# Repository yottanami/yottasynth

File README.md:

# Yottasynth: Open Hardware Touchscreen Synth with Persian/Iranian Tunings

Yottasynth is an open hardware touchscreen synth with a compact page-based control surface, five context-sensitive knobs, an arpeggiator, a step sequencer, and support for Persian/Iranian music tunings.

یوتاسینث یک سینت‌سایزر دیجیتال متن‌باز با رابط لمسی، سکوئنسر، آرپژیاتور و پشتیبانی از کوک‌های موسیقی ایرانی است. این ساز امکان انتخاب کوک‌های مرتبط با دستگاه‌ها و آوازهای ایرانی را فراهم می‌کند تا برای اجرا و طراحی صدا در فضای موسیقی ایرانی مناسب‌تر باشد.

## What It Is

The current firmware is a playable mono synth instrument with:

- a touch-first panel UI
- five context-sensitive knobs
- arpeggiator
- 16-step sequencer
- three effect modes: `Echo`, `Reverb`, and `Drive`
- selectable Persian scale tunings

## Current Features

- `PLAY`, `OSC`, `FILT`, `MOD`, `FX`, `ARP`, `SEQ`, and `SET` pages
- mono synth voice with dual oscillators, noise, filter, envelope, glide, and LFO
- page-specific touch actions and knob mappings
- internal BPM transport, or external MIDI clock sync over USB
- arpeggiator with mode, division, gate, octave range, and latch
- 16-step sequencer with step selection, bank switching, swing, and live MIDI record
- effect editing with page-dependent controls
- output volume, tuning, and clock-source (internal / external) selection from the settings page
- Persian scale support through alternate tunings
- touch screen used for navigation and `OK / Confirm` actions

## Persian / Iranian Tunings

The current tuning list includes:

- `Standard` (`استاندارد`)
- `Shur` (`شور`)
- `Abuata` (`ابوعطا`)
- `Dashti` (`دشتی`)
- `Bayat-e Tork` (`بیات ترک`)
- `Afshari` (`افشاری`)
- `Segah` (`سه‌گاه`)
- `Chahargah` (`چهارگاه`)
- `Homayun` (`همایون`)
- `Bayat-e Esfahan` (`بیات اصفهان`)
- `Nava` (`نوا`)
- `Mahur` (`ماهور`)
- `Rast-Panjgah` (`راست‌پنجگاه`)

## How It Works

Yottasynth is organized as one compact panel split into pages. The touch screen is used to switch pages and trigger actions, while the five physical knobs always control the five parameters shown on screen for the current page.

In normal use, a MIDI controller feeds notes into the synth engine through USB host MIDI. You shape the sound on the synth pages, switch to `ARP` for rhythmic note patterns, use `SEQ` for step programming and live record, and adjust global volume or tuning in `SET`. When a destructive action needs confirmation, a second tap on the armed button acts as `OK`.

The transport (sequencer and arpeggiator) normally runs on its own internal BPM. Set `SYNC` to `EXT` on the `SET` page to slave it to an external MIDI clock over USB instead. Two USB paths are supported without any hardware change:

- the **USB host port** (alongside the keyboard, through a USB hub) for standalone gear such as an Ableton Move
- the **native USB port** (the same cable used to upload firmware) for a computer / DAW such as Ableton Live

In external mode the synth follows the host's tempo and its start / stop / continue transport.

## Interface Summary

- top bar: page title plus compact status
- middle panel: parameter cards and touch actions
- bottom bar: eight color-coded tabs

Page layout:

- `PLAY`: quick performance controls
- `OSC`: oscillator mix, noise, octave, detune, and waveform changes
- `FILT`: filter and envelope shaping
- `MOD`: LFO, bend range, and modulation target
- `FX`: echo, reverb, or drive editing
- `ARP`: arpeggiator setup
- `SEQ`: 16-step sequencing
- `SET`: output volume, tuning, clock source (internal / external sync), and input test entry

## User Guide

For a user-perspective walkthrough of the panel, controls, pages, and sequencing flow, see [docs/user-guide.md](docs/user-guide.md).

For developer-facing documentation of the firmware structure and code, see:

- [docs/README.md](docs/README.md)
- [docs/source-reading-guide.md](docs/source-reading-guide.md)
- [docs/codebase-guide.md](docs/codebase-guide.md)

## Screenshots

To export screenshots of the current screen pages without running the device firmware:

```bash
python3 scripts/generate_screenshots.py
```

This writes one SVG per page, a stitched `overview.svg` for the README, and a simple preview index into `docs/screenshots/`.

## Hardware + 3D

- board design files: `etc/board/`
- touch-driven panel firmware: `src/`
- headers and shared definitions: `include/`
- project docs: `docs/`

## Status

This is still an active work-in-progress project, but the firmware already implements the main instrument shell and core performance workflow.

## Contributing

Contributions are welcome. Feel free to open an issue or a PR if you want to help with firmware, hardware, or design.

## Issues

https://github.com/yottanami/yottainst/issues/new

## Contact

https://yottanami.com

## Support

- GitHub Sponsors: https://github.com/sponsors/yottanami
- Ko-fi: https://ko-fi.com/yottanami

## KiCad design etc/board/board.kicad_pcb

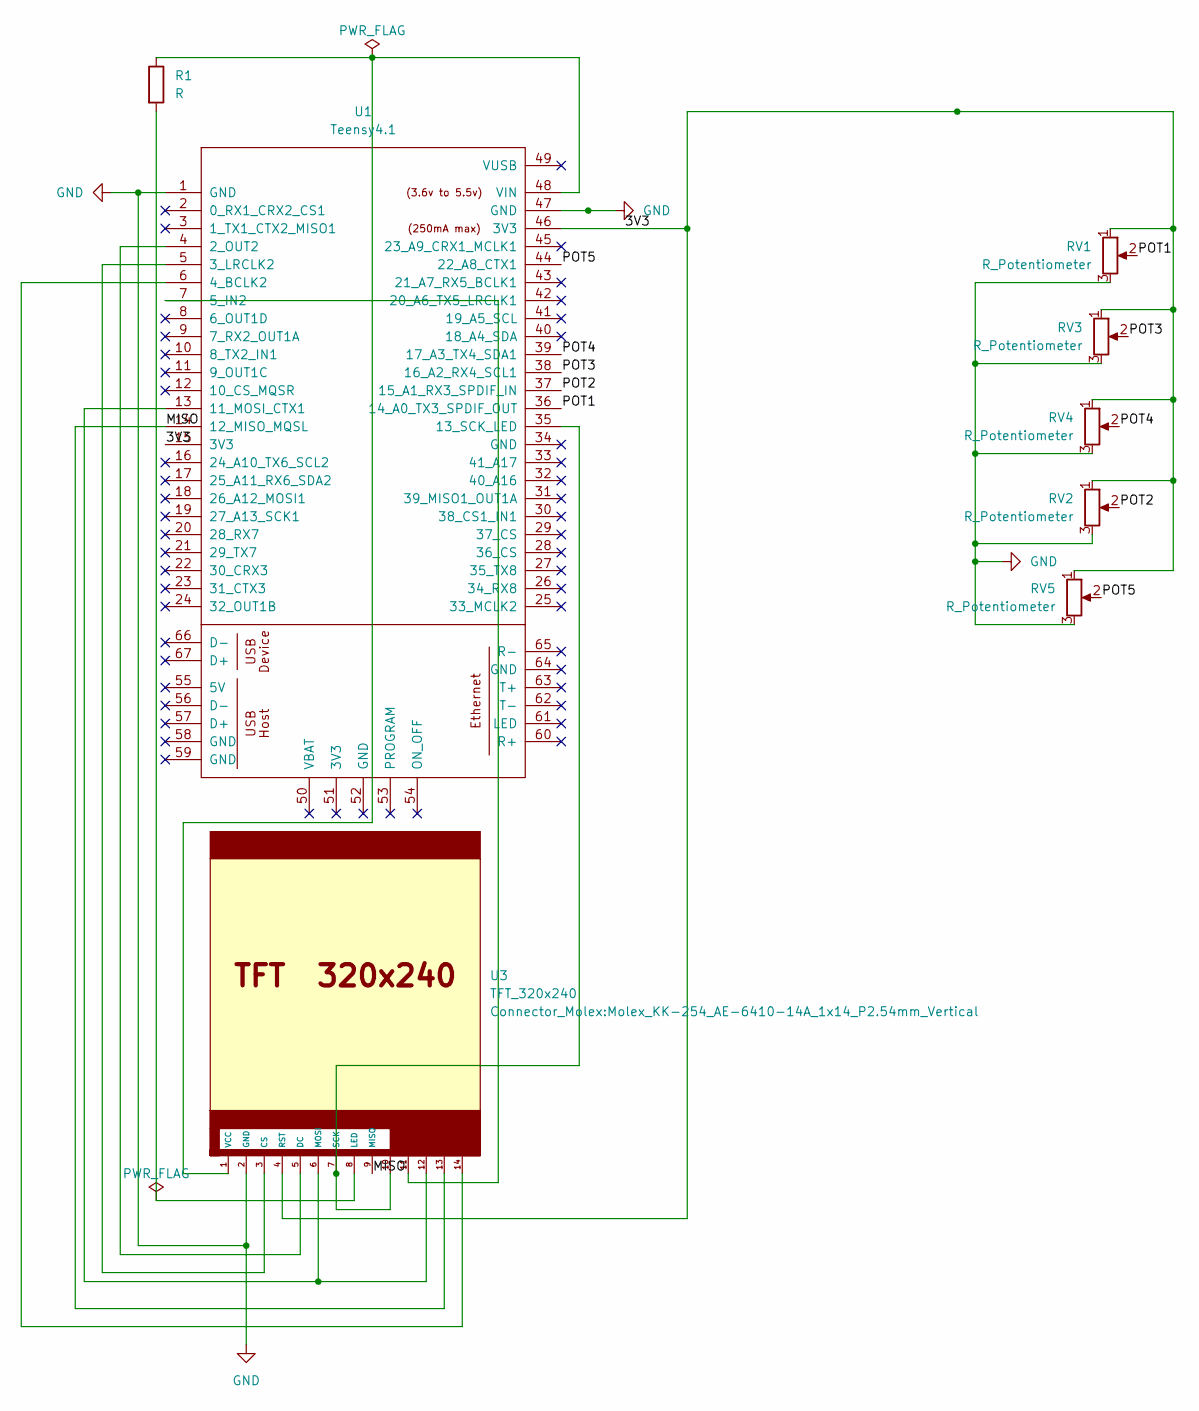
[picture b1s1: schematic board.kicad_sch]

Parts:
R1: R; R_Axial_DIN0207_L6.3mm_D2.5mm_P2.54mm_Vertical
RV1, RV2, RV3, RV4, RV5: R_Potentiometer; Molex_KK-254_AE-6410-03A_1x03_P2.54mm_Vertical
U1: Teensy4.1; Teensy
U3: TFT_320x240; Molex_KK-254_AE-6410-14A_1x14_P2.54mm_Vertical

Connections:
/3V3: RV1.1, RV2.1, RV3.1, RV4.1, RV5.1, U1.15 (3V3), U1.46 (3V3), U3.4 (RST)
/MISO: U1.14 (12_MISO_MQSL), U3.9 (MISO), U3.13
/POT1: RV1.2, U1.36 (14_A0_TX3_SPDIF_OUT)
/POT2: RV2.2, U1.37 (15_A1_RX3_SPDIF_IN)
/POT3: RV3.2, U1.38 (16_A2_RX4_SCL1)
/POT4: RV4.2, U1.39 (17_A3_TX4_SDA1)
/POT5: RV5.2, U1.44 (22_A8_CTX1)
GND: RV1.3, RV2.3, RV3.3, RV4.3, RV5.3, U1.1 (GND), U1.47 (GND), U3.2 (GND)
unnamed: U1.4 (2_OUT2), U3.5 (DC)
unnamed: U1.5 (3_LRCLK2), U3.3 (CS)
unnamed: U1.6 (4_BCLK2), U3.14
unnamed: U1.7 (5_IN2), U3.11
unnamed: U1.13 (11_MOSI_CTX1), U3.6 (MOSI), U3.12
unnamed: U1.35 (13_SCK_LED), U3.7 (SCK), U3.10
unnamed: R1.1, U1.48 (VIN), U3.1 (VCC)
unnamed: R1.2, U3.8 (LED)

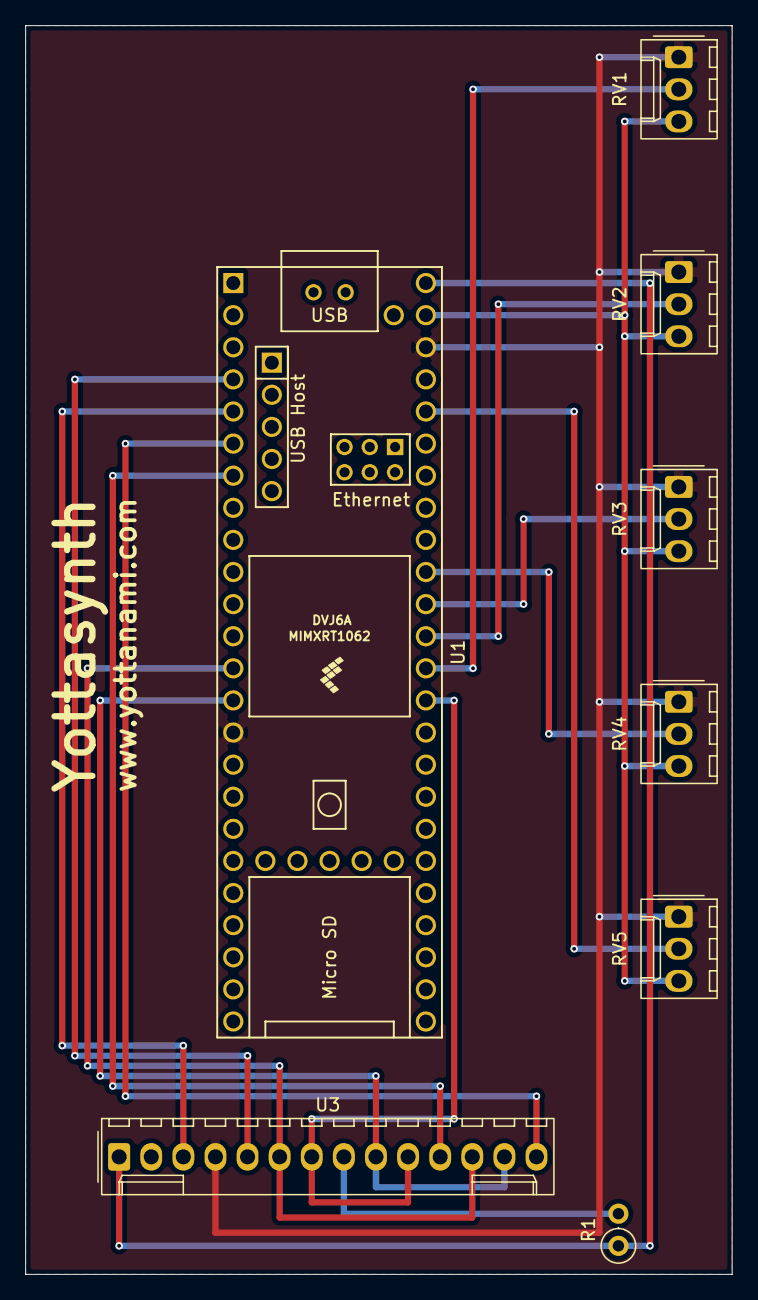
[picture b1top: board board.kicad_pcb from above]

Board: 2 copper layers, 55.9 x 98.8 mm, 8 parts (0 on the bottom side), 16 nets.

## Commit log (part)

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2026-01-29 Remove old board and update README
2026-01-29 Upgrade lvgl
2026-01-29 Update config for new lvgl
2026-01-30 Add soft reboot
2026-04-14 Add Agent file
2026-04-15 uncommit old debug values
2026-04-26 Update board files and scan knob rotates
2026-04-26 Update PINS guide
2026-04-27 Add test page
2026-04-27 Update PINS
2026-04-27 implement first version
2026-04-30 Fix ghost scroll
2026-04-30 Add volume control
2026-04-30 Fix ui and sequencer issues
2026-04-30 Add persian tunning
2026-04-30 Add FX
2026-05-01 Add wave shape control
2026-05-01 Fix after arp issue
2026-05-02 Stable screen touches
2026-05-04 Fix sequencer ghost touch issue
2026-05-04 Update Agents and plans
2026-05-04 Update Agents plans and READme file
2026-05-04 Update README and add persian names of tunings
2026-05-04 Add screenshot generator and update docs based on that
2026-06-29 Add external sync support
